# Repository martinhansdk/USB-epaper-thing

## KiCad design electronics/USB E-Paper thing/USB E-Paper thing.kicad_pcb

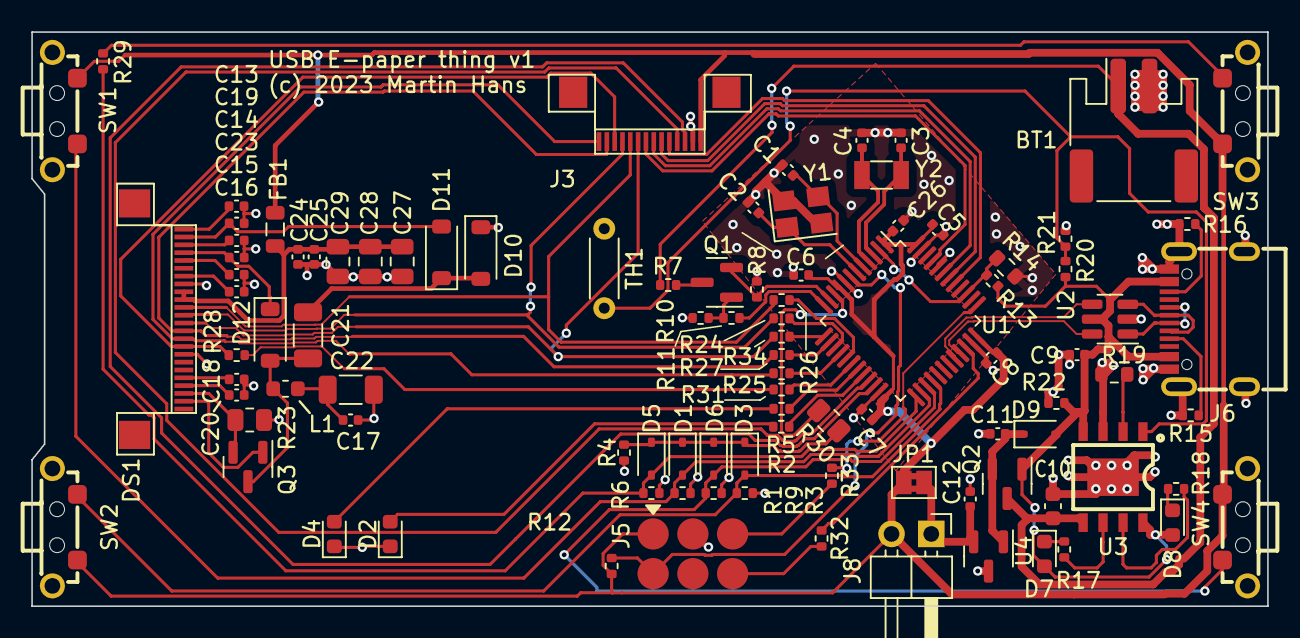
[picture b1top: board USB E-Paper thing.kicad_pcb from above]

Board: 2 copper layers, 79.0 x 36.7 mm, 98 parts (0 on the bottom side), 76 nets.

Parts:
BT1: Battery_Cell; JST_PH_S2B-PH-SM4-TB_1x02-1MP_P2.00mm_Horizontal
C1, C2: 20pF; C_0402_1005Metric
C3, C4: 12p; C_0402_1005Metric
C5, C6, C7, C9, C25, C26: 100n; C_0402_1005Metric
C8, C11, C12: 1u; C_0402_1005Metric
C10: 10u; C_0603_1608Metric
C13, C24: 1u/6V; C_0402_1005Metric
C14, C15, C16, C17, C18, C19, C20, C23: 1u/25V; C_0402_1005Metric
C21: 4.7u/50V; C_1206_3216Metric
C22: 10u/50V; C_1206_3216Metric
C27, C28, C29: 47u/6V; C_0805_2012Metric
D1, D3, D5, D6, D9: 1N5819WS; D_SOD-323
D2: BLUE; LED_0603_1608Metric
D4: YELLOW; LED_0603_1608Metric
D7: GREEN; LED_0603_1608Metric
D8: RED; LED_0603_1608Metric
D10, D11, D12: B5819W; D_SOD-123
DS1: E-PAPER; CONN_FPC_24_AFC24-S24FIA-00
FB1: FerriteBead; L_0805_2012Metric
J3: EXTRA2; FPC_14
J5: SWD; Spring_loaded_connector_land_pattern_02x03
J6: USB 2.0 right angle; USB-C-SMD_G-SWITCH_GT-USB-7010ASV
J8: POWER_MEASUREMENT; PinHeader_1x02_P2.54mm_Horizontal
JP1: SolderJumper_2_Bridged; SolderJumper-2_P1.3mm_Bridged2Bar_Pad1.0x1.5mm
L1: 47uH; L_0603_1608Metric
Q1, Q3: AO3400A; SOT-23
Q2: AO3401A; SOT-23
R1, R3, R4, R6, R7, R8, R9, R10, R12: 10k; R_0402_1005Metric
R2, R24, R25, R26, R27, R28, R32, R33, R34: 33; R_0402_1005Metric
R5: 50; R_0402_1005Metric
R11: 10; R_0402_1005Metric
R13: 33k; R_0402_1005Metric
R14: 82k; R_0603_1608Metric
R15, R16, R20: 5k1; R_0402_1005Metric
R17, R18: 1k; R_0402_1005Metric
R19: 18k; R_0603_1608Metric
R21, R22: 100k; R_0402_1005Metric
R23: 4.7; R_0805_2012Metric
R29, R31: 0R; R_0402_1005Metric
R30: 0R; R_0805_2012Metric
SW1: BUTTON0; KEY-TH_K2-1112SW-AXXW-XX
SW2: BUTTON1; KEY-TH_K2-1112SW-AXXW-XX
SW3: BUTTON2; KEY-TH_K2-1112SW-AXXW-XX
SW4: BUTTON3; KEY-TH_K2-1112SW-AXXW-XX
TH1: Thermistor_NTC; R_Axial_DIN0204_L3.6mm_D1.6mm_P5.08mm_Horizontal
U1: STM32L151C8TxA; LQFP-48_7x7mm_P0.5mm
U2: USBLC6-2SC6; SOT-23-6
U3: TP4056; ESOP-8_L4.9-W3.9-P1.27-LS6.0-BL-EP
U4: ME6216 3V0; SOT-23
Y1: 12 MHz; Crystal_SMD_3225-4Pin_3.2x2.5mm
Y2: 32.768 kHz; Crystal_SMD_3215-2Pin_3.2x1.5mm

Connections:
+3V0: C5.1, C6.1, C7.1, C8.1, C26.1, FB1.2, J3.1, J5.1, J8.2, JP1.2 (B), R12.1, SW1.1, SW2.2, SW3.1, SW4.2, U1.1 (VLCD), U1.9 (VDDA), U1.24 (VDD), U1.36 (VDD), U1.48 (VDD)
+BATT: BT1.1 (+), C10.1, Q2.3 (D), R7.1, U3.5 (BAT)
/BUSY: R28.2, R31.2
/BUSY_DBG: DS1.9 (BUSY), J3.12, R28.1
/BUTTON0: D1.2 (A), R1.1, SW1.2, U1.26 (PB13)
/BUTTON1: D3.2 (A), R3.1, SW2.1, U1.28 (PB15)
/BUTTON2: D5.2 (A), R6.1, R29.1, U1.25 (PB12)
/BUTTON3: D6.2 (A), R9.1, SW4.1, U1.27 (PB14)
/D/~C: DS1.11 (D/C#), J3.13, R27.2
/E-Ink display/GDR: DS1.2 (GDR), Q3.1 (G)
/E-Ink display/PREVGH: C23.1, D12.1 (K), DS1.21 (PREVGH)
/E-Ink display/PREVGL: C19.1, D11.2 (A), DS1.23 (PREVGL)
/E-Ink display/RESE: DS1.3 (RESE), Q3.2 (S), R23.2
/E-Ink display/VCC: C24.1, C25.1, C27.1, C28.1, C29.1, DS1.15 (VDDIO), DS1.16 (VCI), FB1.1
/E-Ink display/VCI: C17.1, C22.1, L1.2
/E-Ink display/VCOM: C13.1, DS1.24 (VCOM)
/E-Ink display/VDD: C16.1, DS1.18 (VDD)
/E-Ink display/VGH: C18.1, DS1.5 (VGH)
/E-Ink display/VGL: C20.1, DS1.4 (VGL)
/E-Ink display/VSH: C15.1, DS1.20 (VSH)
/E-Ink display/VSL: C14.1, DS1.22 (VSL)
/LED0: R5.1, U1.19 (PB1)
/LED1: R2.1, U1.20 (PB2)
/MOSI: DS1.14 (D1), J3.10, R26.2
/NRST: J5.6, R12.2, U1.7 (NRST)
/PB5: J3.5, U1.41 (PB5)
/PB6: J3.6, U1.42 (PB6)
/PB7: J3.7, U1.43 (PB7)
/PB8: J3.8, U1.45 (PB8)
/Power/CC1: J6.A5 (CC1), R15.1
/Power/CC2: J6.B5 (CC2), R16.1
/Power/USB_IN_D+: J6.A6 (D+), J6.B6 (D+), U2.1 (I/O1)
/Power/USB_IN_D-: J6.A7 (D-), J6.B7 (D-), U2.3 (I/O2)
/SCLK: DS1.13 (D0), J3.11, R24.2
/SERIAL_RX: J3.3, U1.22 (PB11)
/SERIAL_TX: J3.4, U1.21 (PB10)
/SWDCLK: J5.3, R33.2
/SWDIO: J5.4, R32.2
/USB_D+: U1.33 (PA12), U2.6 (I/O1)
/USB_D-: U1.32 (PA11), U2.4 (I/O2)
/VBAT_MEAS: Q1.2 (S), R8.1, U1.11 (PA1)
/VBAT_MEAS_EN: R11.2, U1.12 (PA2)
/VBUS: C9.1, D7.2 (A), D8.2 (A), D9.2 (A), J6.A4 (VBUS), J6.A9 (VBUS), J6.B4 (VBUS), J6.B9 (VBUS), Q2.1 (G), R13.1, R20.1, R22.1, U2.5 (VBUS), U3.4 (VCC), U3.8 (CE)
/VBUS_PRESENT: R13.2, R14.1, U1.2 (PC13), U1.39 (PB3)
/WAKEUP: R30.1, U1.10 (PA0)
/~CS: DS1.12 (CS#), J3.9, R34.2
/~RES: DS1.10 (RES#), J3.14, R25.2
GND: BT1.2 (-), C1.2, C2.2, C3.2, C4.2, C5.2, C6.2, C7.2, C8.2, C9.2, C10.2, C11.2, C12.2, C13.2, C14.2, C15.2, C16.2, C17.2, C18.2, C19.2, C20.2, C22.2, C23.2, C24.2, C25.2, C26.2, C27.2, C28.2, C29.2, D2.1 (K), D4.1 (K), D10.1 (K), DS1.8 (BS1), DS1.17 (VSS), J3.2, J5.2, J6.A1 (GND), J6.A12 (GND), J6.B1 (GND), J6.B12 (GND), J6.S1 (SHIELD), R1.2, R3.2, R4.2, R6.2, R8.2, R9.2, R10.1, R14.2, R15.2, R16.2, R19.2, R21.2, R22.2, R23.1, TH1.1, U1.8 (VSSA), U1.23 (VSS), U1.35 (VSS), U1.44 (BOOT0), U1.47 (VSS), U2.2 (GND), U3.3 (GND), U3.9 (THERMAL), U4.3 (GND), Y1.2, Y1.4
unnamed: D1.1 (K), D3.1 (K), D5.1 (K), D6.1 (K), R4.1, R30.2
unnamed: D2.2 (A), R2.2
unnamed: D4.2 (A), R5.2
unnamed: D7.1 (K), R17.1
unnamed: D8.1 (K), R18.1
unnamed: C11.1, D9.1 (K), Q2.2 (S), U4.1 (IN)
unnamed: C21.2, D10.2 (A), D11.1 (K)
unnamed: C21.1, D12.2 (A), L1.1, Q3.3 (D)
unnamed: C12.1, J8.1, JP1.1 (A), U4.2 (OUT)
unnamed: Q1.3 (D), R7.2
unnamed: Q1.1 (G), R10.2, R11.1
unnamed: R29.2, SW3.2
unnamed: R34.1, U1.13 (PA3)
unnamed: R27.1, U1.14 (PA4)
unnamed: R24.1, U1.15 (PA5)
unnamed: R25.1, U1.16 (PA6)
unnamed: R26.1, U1.17 (PA7)
unnamed: R32.1, U1.34 (PA13)
unnamed: R33.1, U1.37 (PA14)
unnamed: R31.1, U1.18 (PB0)
unnamed: C3.1, U1.3 (PC14), Y2.2
unnamed: C4.1, U1.4 (PC15), Y2.1
unnamed: C1.1, U1.5 (PH0), Y1.3
unnamed: C2.1, U1.6 (PH1), Y1.1
unnamed: R19.1, U3.2 (PROG)
unnamed: R20.2, R21.1, TH1.2, U3.1 (TEMP)
unnamed: R18.2, U3.7 (~CHRG)
unnamed: R17.2, U3.6 (~STDBY)

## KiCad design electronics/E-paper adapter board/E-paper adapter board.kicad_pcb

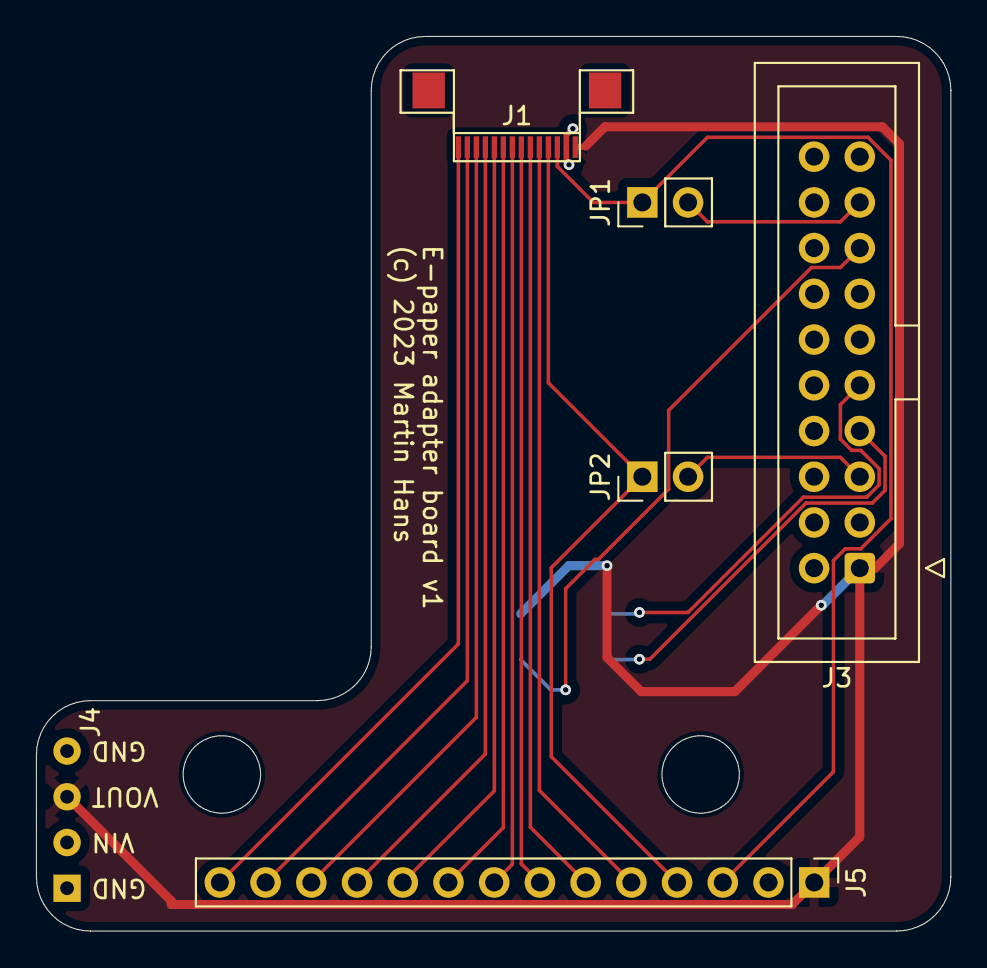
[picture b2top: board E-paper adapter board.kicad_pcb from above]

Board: 2 copper layers, 50.8 x 49.7 mm, 9 parts (1 on the bottom side), 19 nets.

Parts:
H1, H2: MountingHole; MountingHole_4.3mm_M4_DIN965
J1: EXTRA; FPC_14
J2: SWD; E-paper programming connector
J3: J-LINK; IDC-Header_2x10_P2.54mm_Vertical
J4: nRF-PPK2; nRF-PPK2_power
J5: DEBUG; PinHeader_1x14_P2.54mm_Vertical
JP1, JP2: Jumper_2_Bridged; PinHeader_1x02_P2.54mm_Vertical

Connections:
+3V0: J1.1, J2.1, J3.1, J4.3 (VOUT), J5.1
/BUSY: J1.12, J5.12
/D/~C: J1.13, J5.13
/MOSI: J1.10, J5.10
/NRST: J2.6, J3.15
/PB5: J1.5, J5.5
/PB6: J1.6, J5.6
/PB7: J1.7, J5.7
/PB8: J1.8, J5.8
/PG_UART_RXD: J3.5, JP2.2 (B)
/PG_UART_TXD: J3.17, JP1.2 (B)
/SCLK: J1.11, J5.11
/SERIAL_RX: J1.3, J5.3, JP1.1 (A)
/SERIAL_TX: J1.4, J5.4, JP2.1 (A)
/SWDCLK: J2.3, J3.9
/SWDIO: J2.4, J3.7
/~CS: J1.9, J5.9
/~RES: J1.14, J5.14
GND: J1.2, J2.2, J3.4, J3.6, J3.8, J3.10, J3.12, J4.1 (GND), J4.4 (GND), J5.2

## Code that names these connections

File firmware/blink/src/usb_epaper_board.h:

#ifndef USB_EPAPER_BOARD_H
#define USB_EPAPER_BOARD_H

#include <Arduino.h>

#define VBAT_MEAS_PIN PA1
#define VBAT_MEAS_EN_PIN PA2
#define CSN_PIN PA3
#define DC_PIN PA4
#define RESN_PIN PA6
#define BUSY_PIN PB0
#define LED0_PIN PB1
#define LED1_PIN PB2
#define VBUS_PRESENT_PIN PB3
#define BUTTON2_PIN PB12
#define BUTTON0_PIN PB13
#define BUTTON3_PIN PB14
#define BUTTON1_PIN PB15

#endif

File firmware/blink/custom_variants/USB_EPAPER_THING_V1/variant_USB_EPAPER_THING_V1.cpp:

/*
 *******************************************************************************
 * Copyright (c) 2020, STMicroelectronics
 * All rights reserved.
 *
 * This software component is licensed by ST under BSD 3-Clause license,
 * the "License"; You may not use this file except in compliance with the
 * License. You may obtain a copy of the License at:
 *                        opensource.org/licenses/BSD-3-Clause
 *
 *******************************************************************************
 */
#include "pins_arduino.h"

// Digital PinName array
const PinName digitalPin[] = {
  PA_0,   // D0/A0
  PA_1,   // D1/A1
  PA_2,   // D2/A2
  PA_3,   // D3/A3
  PA_4,   // D4/A4
  PA_5,   // D5/A5
  PA_6,   // D6/A6
  PA_7,   // D7/A7
  PA_8,   // D8
  PA_9,   // D9
  PA_10,  // D10
  PA_11,  // D11
  PA_12,  // D12
  PA_13,  // D13
  PA_14,  // D14
  PA_15,  // D15
  PB_0,   // D16/A8
  PB_1,   // D17/A9
  PB_2,   // D18
  PB_3,   // D19
  PB_4,   // D20
  PB_5,   // D21
  PB_6,   // D22
  PB_7,   // D23
  PB_8,   // D24
  PB_9,   // D25
  PB_10,  // D26
  PB_11,  // D27
  PB_12,  // D28/A10
  PB_13,  // D29/A11
  PB_14,  // D30/A12
  PB_15,  // D31/A13
  PC_13,  // D32
  PC_14,  // D33
  PC_15,  // D34
  PH_0,   // D35
  PH_1    // D36
};

// Analog (Ax) pin number array
const uint32_t analogInputPin[] = {
  0,  // A0,  PA0
  1,  // A1,  PA1
  2,  // A2,  PA2
  3,  // A3,  PA3
  4,  // A4,  PA4
  5,  // A5,  PA5
  6,  // A6,  PA6
  7,  // A7,  PA7
  16, // A8,  PB0
  17, // A9,  PB1
  28, // A10, PB12
  29, // A11, PB13
  30, // A12, PB14
  31  // A13, PB15
};

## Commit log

2023-11-06 WIP commit
2023-12-03 Use single FPC connector for debug signals and downstream
2023-12-04 Resistor calculations
2023-12-04 switch to JLCPCB version of USBC connect fp
2023-12-05 Fix all DRC violations, fix 12 MHz crystal connections
2023-12-05 move electronics project to subdir
2023-12-06 add adapter board
2023-12-11 fix TP4056 footprint
2023-12-19 Add STEP files of the boards
2023-12-30 Added blink firmware for board bringup
2023-12-30 Use alternative pin names on STM32 symbol on schematic
2023-12-31 Working board definition based on STM32Duino's generic STM32L151C8T6 board
2023-12-31 Move board definition so they can be shared between platformio projects

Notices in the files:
electronics/E-paper adapter board/E-paper adapter board.kicad_pcb:
(c) 2023 Martin Hans
